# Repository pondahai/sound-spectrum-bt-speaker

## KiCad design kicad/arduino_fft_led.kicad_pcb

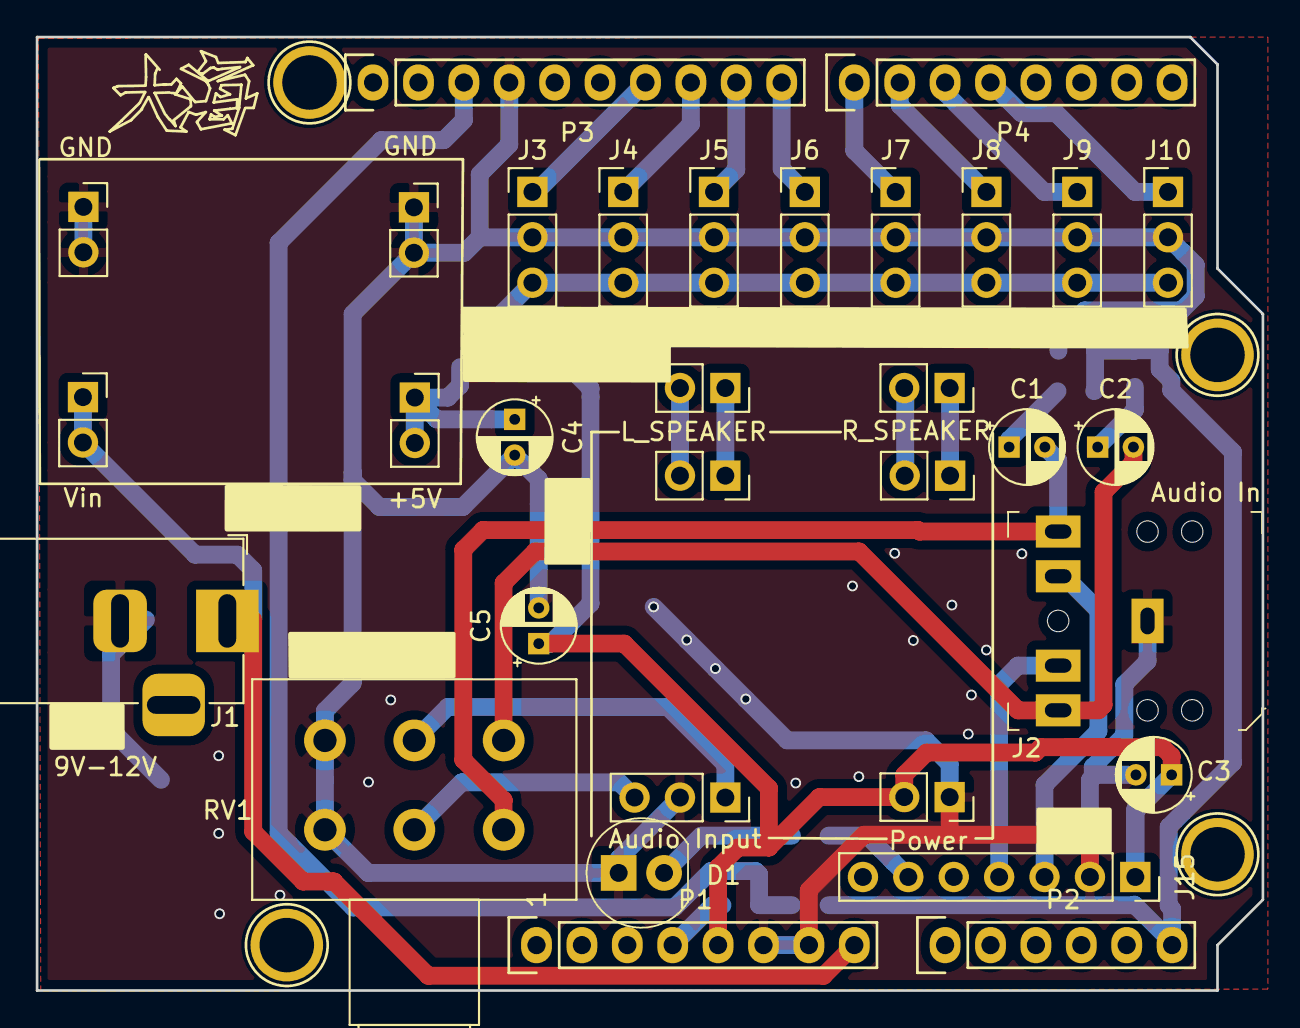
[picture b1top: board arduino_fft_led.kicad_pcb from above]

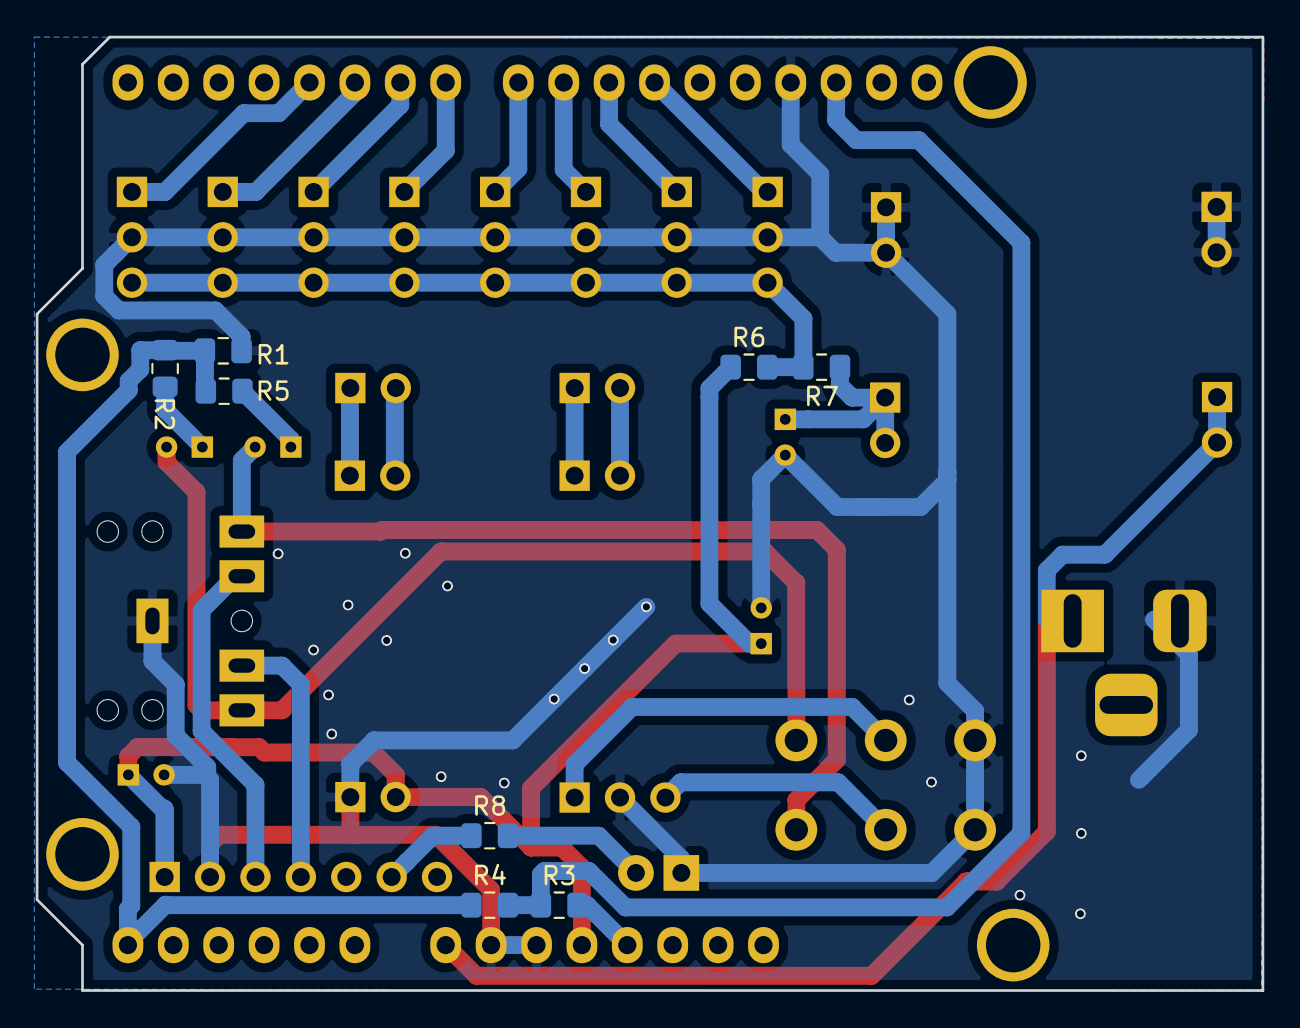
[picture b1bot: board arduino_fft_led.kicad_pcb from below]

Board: 2 copper layers, 68.6 x 53.3 mm, 44 parts (8 on the bottom side), 30 nets.

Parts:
C1, C2: 0.01u; CP_Radial_D4.0mm_P2.00mm
C3, C4, C5: CP1_Small; CP_Radial_D4.0mm_P2.00mm
D1: LED_ALT; LED_5mm_Radial
J1: 9V-12V; BarrelJack_Horizontal
J2: Audio In; audiojack-3.5mm-5p
J3, J4, J5, J6, J7, J8, J9, J10: Conn_01x03_Male; PinHeader_1x03_P2.54mm_Vertical
J11: Vin; PinSocket_1x02_P2.54mm_Vertical
J12, J14: GND; PinSocket_1x02_P2.54mm_Vertical
J13: +5V; PinSocket_1x02_P2.54mm_Vertical
J15: BT Audio; PinSocket_1x07_P2.54mm_Vertical
J16: R_SPEAKER; PinSocket_1x02_P2.54mm_Vertical
J17: L_SPEAKER; PinSocket_1x02_P2.54mm_Vertical
J18: R; PinSocket_1x02_P2.54mm_Vertical
J19: L; PinSocket_1x02_P2.54mm_Vertical
J20: Power; PinSocket_1x02_P2.54mm_Vertical
J21: Audio Input; PinSocket_1x03_P2.54mm_Vertical
P1: Power; Socket_Strip_Arduino_1x08
P2: Analog; Socket_Strip_Arduino_1x06
P3: Digital; Socket_Strip_Arduino_1x10
P4: Digital; Socket_Strip_Arduino_1x08
P5, P6, P7, P8: CONN_01X01; Arduino_1pin
R1, R2, R3: 5k1; R_0805_2012Metric_Pad1.15x1.40mm_HandSolder
R4, R5: 100k; R_0805_2012Metric_Pad1.15x1.40mm_HandSolder
R6, R7: short; R_0805_2012Metric_Pad1.15x1.40mm_HandSolder
R8: 100; R_0805_2012Metric_Pad1.15x1.40mm_HandSolder
RV1: R_POT_Dual; Potentiometer_Alps_RK163_Dual_Horizontal

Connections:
+3V3: P1.4, R3.2
+5V: C3.1, C5.1, J15.1, J20.2, P1.5, R6.1
/4: J10.1, P4.4
/5(**): J9.1, P4.3
/6(**): J8.1, P4.2
/7: J7.1, P4.1
/8: J6.1, P3.10
/9(**): J5.1, P3.9
/10(**/SS): J4.1, P3.8
/11(**/MOSI): J3.1, P3.7
/A5(SCL): P2.6, R1.1, R2.1, R4.1, R5.2
/AREF: P3.3, R3.1, R4.2
/BT_LEFT: J2.TN, J15.3
/BT_RIGHT: J2.RN, J15.4
/LEFT: C1.2, J2.T, RV1.3
/RIGHT: C2.2, J2.R, RV1.6
/Vin: J1.1, J11.1, J11.2, P1.8
GND: C3.2, C4.2, C5.2, D1.1, J1.2, J2.S, J3.2, J4.2, J5.2, J6.2, J7.2, J8.2, J9.2, J10.2, J12.1, J12.2, J14.1, J14.2, J15.2, J20.1, J21.2, P1.6, P1.7, P3.4, R5.1, RV1.1, RV1.4
unnamed: C1.1, R1.2
unnamed: C2.1, R2.2
unnamed: C4.1, J13.1, J13.2, R7.1
unnamed: D1.2, R8.2
unnamed: J3.3, J4.3, J5.3, J6.3, J7.3, J8.3, J9.3, J10.3, R6.2, R7.2
unnamed: J15.6, R8.1
unnamed: J16.1, J18.1
unnamed: J16.2, J18.2
unnamed: J17.1, J19.1
unnamed: J17.2, J19.2
unnamed: J21.1, RV1.5
unnamed: J21.3, RV1.2
